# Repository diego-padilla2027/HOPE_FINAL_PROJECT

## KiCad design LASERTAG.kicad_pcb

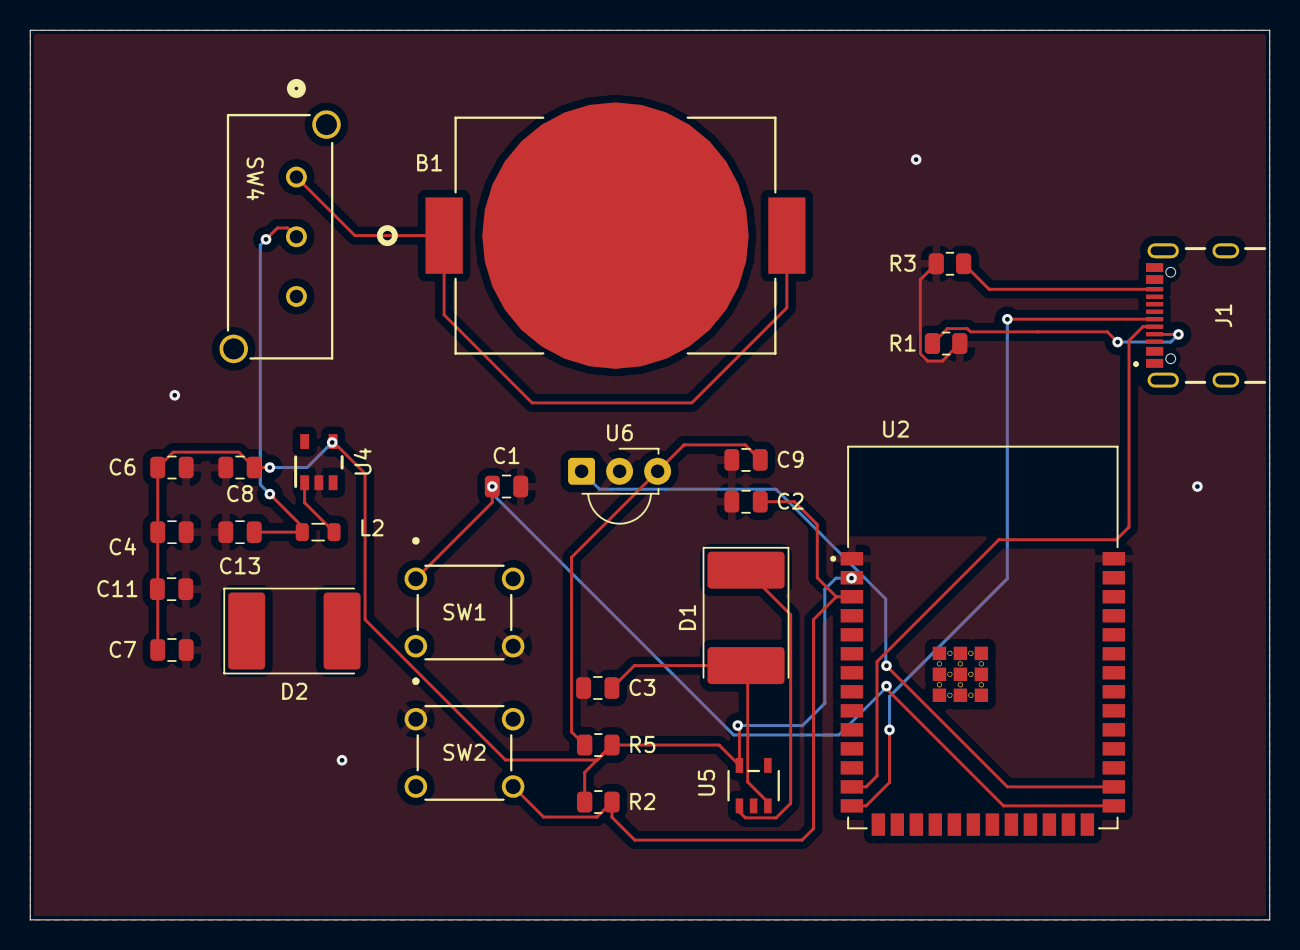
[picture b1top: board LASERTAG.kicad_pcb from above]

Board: 2 copper layers, 82.8 x 59.4 mm, 26 parts (0 on the bottom side), 15 nets.

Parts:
B1: BAT-HLD-001; BATT_HLDR_LNX
C1, C2, C8, C9: .1uF; C_0805_2012Metric
C3, C4, C7: 1uF; C_0805_2012Metric
C6, C11: 10uF; C_0805_2012Metric
C13: 4.7uF; C_0805_2012Metric
D1, D2: D_Schottky; D_3220_8050Metric
J1: USB4105-GF-A; GCT_USB4105-GF-A
L2: 2.2uH; L_0805_2012Metric
R1, R3: 5.1k; R_0805_2012Metric
R2: 10k; R_0805_2012Metric
R5: 100; R_0805_2012Metric
SW1, SW2: B3F-1000; SW_B3F-1000_OMR
SW4: 1825255-1; SW3_1825255-1_TEC
U2: ESP32-S2-SOLO; XCVR_ESP32-S2-SOLO-N4
U4: TPS613221ADBVR; DBV0005A_N
U5: AP7366-33W5-7; SOT25-YE_DIO
U6: TSOP582xx; Vishay_MINICAST-3Pin

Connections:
+3.3V: C4.2, C6.1, C7.1, C8.1, C11.1, R2.1, R5.2, U2.2 (3V3), U4.4 (VOUT), U5.5 (OUT)
+5V: C3.1, D1.2 (A), U5.3 (EN)
/D+: J1.A6 (DP1), J1.B6 (DP2), U2.14 (GPIO20/U1CTS/ADC2_CH9/CLK_OUT1/USB_D+)
/D-: J1.A7 (DN1), J1.B7 (DN2), U2.13 (GPIO19/U1RTS/ADC2_CH8/CLK_OUT2/USB_D-)
GND: B1.2, C1.2, C2.1, C3.2, C4.1, C6.2, C7.2, C8.2, C9.2, C11.2, C13.2, J1.A8 (SBU1), J1.B8 (SBU2), R1.2, R3.1, SW1.4, SW2.1, U2.1 (GND), U2.40 (GND), U4.2 (GND), U5.2 (GND), U6.2 (GND)
unnamed: B1.1, B1.3, SW4.1
unnamed: C13.1, L2.1, SW4.2
unnamed: D1.1 (K), U5.1 (IN)
unnamed: J1.A5 (CC1), R1.1
unnamed: J1.B5 (CC2), R3.2
unnamed: C2.2, R2.2, SW2.4, U2.3 (EN)
unnamed: C1.1, SW1.1, U2.27 (GPIO0)
unnamed: U2.28 (SPIIO6/GPIO35/FSPID), U6.1 (OUT)
unnamed: L2.2, U4.1 (SW)
unnamed: C9.1, R5.1, U6.3 (Vs)

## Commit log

2024-10-31 feedback changes
2024-10-31 rm files
2024-11-02 temp added diff booster, assigned footprints, changes from feedback
2024-11-07 fix a lot of things i don't remember sorryy
